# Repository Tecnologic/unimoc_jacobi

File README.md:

# Jacobi
36 V / 45 A (battery side, 100 A peak phase current) drive hardware of the [unimoc](https://github.com/Tecnologic/unimoc)
project, with optimised cooling. Jacobi is the motor controller (logic board and
power board); the firmware lives in the unimoc repository.

| | |
|---|---|
| Board directory (firmware) | `boards/unimoc/jacobi/` |
| Board name | `unimoc_jacobi` |
| Cyphal node name | `org.unimoc.jacobi` |
| EESM variant | Jacobi E |

Formerly `hardware_4850`.

### Naming

The unimoc nodes are named after inventors. Moritz Hermann Jacobi built the
first practical electric motor (1834, Königsberg) and drove a boat on the Neva
with it (1838): the first electric motor put to practical use as a drive, which
is what this board is for.

**Drives**

| Name | Class | Who |
|---|---|---|
| Barlow | small drive | Peter Barlow, whose "Barlow's wheel" (1822) was one of the first electric motors: tiny but turning |
| **Jacobi** | **36 V / 45 A drive (this board, H7)** | Moritz Hermann Jacobi, first practical electric motor (1834) and electric boat on the Neva (1838) |
| Dolivo | big drive | Michail Dolivo-Dobrowolsky invented the three-phase motor and the three-phase system (AEG, 1889), the basis of every FOC drive |

**Other nodes**

| Name | Role | Who |
|---|---|---|
| Zuse | VDC | Konrad Zuse built the first working programmable computer, so he's the brain |
| Drais | Pedal generator | Karl Drais invented the Laufmaschine (1817), the ancestor of the bicycle, powered by your own feet |
| Mercator | Steering | the map maker everyone navigates by |
| Gutenberg | Display | made information visible to everyone |
| Volta | BMS / battery | invented the battery (the voltaic pile, 1800) |
| Otto | Throttle | Nikolaus Otto, of the Otto engine: the classic gas pedal |

## Ratings and limits

What the hardware can do and where it stops. The numbers come from the
datasheets and rough loss and thermal estimates (calculations below), not from
measurements on a test bench. The reference load is the kids' quad: an MY1020
1600 W BLDC on 3 × 12 V lead-acid, which the controller already drives with
80 A peak phase current.

| | Rating | Limited by |
|---|---|---|
| Battery | **3 × 12 V lead-acid (36 V)**, up to 44 V while charging; Li-ion up to 10S (42 V) | 60 V FETs (NCEP6080AG), see below |
| Enable input (J501 pin 3 against pin 4) | **12–40 V**, switched battery voltage; 1–4 mA through a TLP291 optocoupler, 3750 Vrms isolation | input resistor R1115 (10k, 1206): 0.19 W at 44 V, 0.25 W rating |
| Battery current | **~45 A** (1600 W at 36 V) for minutes in still air; continuous only with better cooling | housing to air: 1600 W needs about 58 A peak phase current |
| Phase current, peak | **100 A** for seconds | motor saturation, FET losses |
| Phase current, continuous | **~50 A peak** in still air; with the housing bolted to a frame or in airflow, the 100 A motor limit comes first | housing to air (about 2.5 K/W) |
| Overcurrent trip | **120–130 A** | current sensing range ±160 A |
| Not suitable for | 48 V systems (13S/14S Li-ion, 4 × 12 V lead-acid) | 60 V FET rating |

### Target motors

| Motor | Saturation (peak phase current) | Fit |
|---|---|---|
| 60 mm stator motors | ~100 A | up to the rating |
| Hoverboard hub motors | ~55 A | about a third of the current range, fine resolution |
| MY1020 1600 W, 36 V (kids' quad) | not published, estimated 80–100 A | runs today at 80 A peak |

The MY1020 has no published saturation data. It can be measured with the
controller: lock the rotor, run a DC current on the d or q axis in steps
(0, 20, 40 … 120 A) and measure L = V / (di/dt) with a small voltage pulse.
Saturation starts where L falls by 20–30 %. Above that current the motor gives
little extra torque and mostly heat, so it is the useful current limit.

### Bridge voltage: why 36 V

The bridge uses **NCEP6080AG** (NCE, LCSC `C182469`, DFN5×6-8L), two in
parallel per switch, 12 per board. They are in stock and cost much less than
an 80 V part. From the LCSC product page (the datasheet PDF was not
reachable): 60 V, 80 A, R_DS(on) < 4.0 mΩ at 10 V (3.5 mΩ typ),
< 5.0 mΩ at 4.5 V, Qg 67 nC, Coss 680 pF, 85 W, Tj up to 150 °C.

| Battery | Max voltage | Margin to 60 V |
|---|---|---|
| 3 × 12 V lead-acid | ~44 V (charging) | 16 V: **fine** |
| 10S Li-ion | 42 V | 18 V: **fine** |
| 13S Li-ion | 54.6 V | 5 V: switching overshoot alone can use that, **no** |
| 14S Li-ion / 4 × 12 V | 58.8 V / ~58 V | **no** |

For 48 V the bridge needs 80 V FETs in the same footprint, e.g. the Infineon
**BSC040N08NS5** (80 V, 4.0 mΩ max, 121 A, marking `040N08NS`), which sits on
one of the existing prototype boards. Its R_DS(on) is the same as the NCE part;
its lower gate charge (43 nC) only shortens the switching edges a little. The
rest of the board already handles 48 V: the LM5008 supply runs from the battery
up to 95 V, and the voltage dividers reach 73.8 V full scale.

### Bridge losses

Two FETs in parallel per switch, sine current, 36 V, 20 kHz PWM, about 45 ns
switching edges (LM5109B at about 1 A into 2 × 67 nC, 1R1 gate resistors).
R_DS(on) is 4.0 mΩ max × 1.6 for Tj = 125 °C ≈ 6.4 mΩ. The factor 1.6 is
taken from the BSC040N08NS5 curve because the NCE datasheet was not
available; check it once the datasheet is in `datasheets/`.

| Phase current (peak) | Loss per FET | Loss per phase | Whole bridge |
|---|---|---|---|
| 50 A | ~1.3 W | ~5 W | ~16 W |
| 80 A | ~3 W | ~12 W | ~36 W |
| 100 A | ~4.5 W | ~18 W | ~54 W |

Conduction per FET is I_rms² × R_DS(on) / 8 (the phase current splits over two
FETs, and high and low side each conduct about half the time). Switching per
phase is ½ × V × I_avg × (t_on + t_off) × f_PWM with I_avg = 2/π × I_peak.

Using one FET per switch instead of two would save 6 FETs and about 180 mm²,
but it doubles the conduction loss at the same current (about 16 W per FET at
100 A peak). In the closed housing that comes straight off the continuous
current, so the board keeps two per switch.

### PCB manufacturing

The board is made by JLCPCB: 4 layers, **1 oz copper** on all layers (outer and
inner), standard process. The design rules in `jacobi.kicad_pro` follow the
[JLCPCB 4-layer capabilities](https://jlcpcb.com/capabilities/pcb-capabilities):

| Rule | Value |
|---|---|
| Min track width / clearance | 0.1 mm / 0.1 mm (the layout uses 0.2 mm / 0.2 mm or more) |
| Min via (diameter / drill) | 0.45 mm / 0.2 mm, annular ring 0.125 mm (the layout uses 0.6 / 0.3 mm and 0.8 / 0.4 mm) |
| Min copper to board edge | 0.3 mm (board setup: 0.5 mm) |
| Min hole to hole / hole clearance | 0.25 mm |
| Min silk text | 1.0 mm high, 0.15 mm line |

Net classes set the routing defaults (the high-current nets use pours, the track
width is only for stubs and pad entries):

| Class | Track / clearance / via | Nets |
|---|---|---|
| Power | 1.0 / 0.25 / 0.8 ⌀ 0.4 mm | +BATT, GNDPWR, phase and switch nodes |
| GateDrive | 0.5 / 0.2 / 0.6 ⌀ 0.3 mm | +12P, gate, HO/LO/HS/VSS, bootstrap |
| Dig Supply | 0.4 / 0.2 / 0.6 ⌀ 0.3 mm | +12V, +3V3, +1V2, +BATT_LOGIC, GNDD, buck nodes |
| Analog Supply | 0.4 / 0.2 / 0.6 ⌀ 0.3 mm | +3.3VA, +3.3VADC, GNDA, GND |
| Analog | 0.2 / 0.2 / 0.45 ⌀ 0.2 mm | current and voltage sense, temperature, ADC inputs |
| USB | 0.2 / 0.2 mm, pair gap 0.15 mm | USB_DP, USB_DM (impedance not yet checked) |
| Default | 0.15 / 0.15 / 0.45 ⌀ 0.2 mm | everything else |

### Cooling

The power board sits on an aluminium block the size of the board, which is
mounted to the floor of the G113T housing (115 × 90 mm). Today the bottom
copper is covered by solder mask, with thermal paste to the block and a
thermal pad to the housing.

| Step (per FET unless noted) | Rth | Note |
|---|---|---|
| Junction → case | ~1 K/W | datasheet class value |
| **Thermal vias** | **~3.3 K/W** | 38 × 0.4 mm, 25 µm plating: the largest step from FET to block |
| Solder mask + paste | ~1 K/W | 20 µm mask, 50 µm paste over about 100 mm² |
| Junction → block | **~5.5 K/W** | about 17 K at 80 A peak, about 25 K at 100 A peak |
| Block → housing (pad, whole board) | 0.05–0.1 K/W | 3–5 K at 54 W |
| **Housing → air (whole board)** | **~2–3 K/W** | 0.043 m² of housing in still air: **sets the continuous current** |

At 80 A peak the bridge loses about 36 W. In still air the housing would end up
far above any sensible temperature; it works because the peaks are short. The
block and housing hold about 600 J/K (10 mm block assumed), a time constant of
about 25 minutes, so 54 W (100 A peak) heats them by about 5 K per minute.

Continuous current for a block at ≤ 80 °C at 40 °C ambient (40 K):

| Housing to air | Allowed loss | Continuous phase current |
|---|---|---|
| Still air, ~2.5 K/W | ~16 W | ~50 A peak |
| Bolted to the frame or in airflow, ~0.5 K/W | ~80 W | ~120 A peak, so the 100 A motor limit comes first |

Improvements, biggest first:

1. **Housing to air.** Bolt the housing to the vehicle frame or a metal plate
   with paste, or add fins or airflow. This is worth more than all other steps
   together.
2. **Thermal vias.** Filled and capped vias (VIPPO) under the drain pad, as many
   as fit: about half the 3.3 K/W. The board stays 1 oz copper; the currents are
   carried by pours on all four layers, not by thicker copper.
3. **Block to housing.** Thin paste on flat surfaces instead of the thermal pad,
   screws near the FET rows.
4. **Copper spreading.** Large drain pours under each FET on the bottom and
   inner layers.

**Keep the isolation.** The bottom copper under the high-side FETs is at
+BATT, under the low-side FETs it is the phase node, and the block conducts.
The solder mask is the only insulation today. Opening the mask needs a defined
insulator instead (25 µm polyimide film or a 0.15–0.2 mm ceramic-filled pad);
thermally that is about the same as mask and paste, but the isolation is
reliable. Avoid metal-filled pastes there.

### Current sensing

One 0.5 mΩ 3920 shunt per phase (Yezhan DSLR-M-5-0.5F) in the phase output,
with an INA240A1 (gain 20):

| | |
|---|---|
| Range | 1.6 V / (20 × 0.5 mΩ) = **±160 A**, 10 mV/A |
| Overcurrent trip | 120–130 A, above the 100 A motor saturation |
| Offset | 25 µV max at the input = 0.05 A; calibrated at start, drift 0.25 µV/K |
| Resolution | about 0.08 A at 12 effective bits |
| Shunt loss | 1.6 W at 80 A peak, 2.5 W at 100 A peak (9 W part) |

Other combinations that were considered:

| Shunt + INA240 | Range | Why not |
|---|---|---|
| 0.4 mΩ + A1 | ±200 A | only needed for currents above 130 A, which the motors cannot use |
| 0.2 mΩ + A2 | ±160 A | same scaling, but 2.5× the offset in amps, and the A2 costs 1.60 € vs 0.25 € for a shunt |
| 0.2 mΩ + A1 | ±400 A | coarse at light load (about 0.2 A noise) |

## KiCad project

The logic board and the power board are combined in a single **KiCad 10** project:
[`jacobi.kicad_pro`](jacobi.kicad_pro).

| File | Content |
|---|---|
| [`jacobi.kicad_sch`](jacobi.kicad_sch) | Root sheet with the two board sheets |
| [`logic.kicad_sch`](logic.kicad_sch) | Logic board: sub-sheets [`power_supply`](power_supply.kicad_sch) and [`controller`](controller.kicad_sch); `controller` has the sub-sheets [`interfaces`](interfaces.kicad_sch) and [`analog`](analog.kicad_sch) |
| [`power.kicad_sch`](power.kicad_sch) | Power board: sub-sheet [`phase`](phase.kicad_sch), used three times for phase A/B/C |
| [`jacobi.kicad_pcb`](jacobi.kicad_pcb) | Both boards side by side: logic board on the left, power board on the right |
| [`footprints/jacobi.pretty`](footprints/jacobi.pretty) | Project footprint library: enclosure RND 455-00370, the Kelvin footprint of the phase shunt `R_Shunt_Yezhan_DSLR-5_3920_Kelvin`, and `LFPAK56_ThermalVias-1` and `C_2220_5650Metric`, which KiCad 10 no longer ships |

Since both boards are in one PCB file, the net names are kept apart by the
schematic hierarchy (`/logic/...`, `/power/...`). The board-to-board connectors
(J101/J102/J111 on the logic board, J103/J104/J110 on the power board) are **not** joined
electrically in the schematic, so each board keeps its own nets.

## PCB layout (rev 0.3)

Both boards are placed and routed for the released schematic (STM32H743
logic board, three-phase power board). DRC with schematic parity has no
errors and no open connections. Pictures: [logic board](docs/logic_board.png),
[its four layers](docs/logic_board_layers.png), [power board](docs/power_board.png),
[its four layers](docs/power_board_layers.png).

**Mechanics.** The logic board sits on top of the power board (104.05 mm apart
in x in the PCB file). The three M3 standoffs go through H104/H105/H107 (power)
and H102/H101/H103 (logic); H106 and the four housing pads of N101 screw the
power board to the cooling block. None of these moved. The three 2×5 pairs
J101/J103, J102/J104 and J111/J110 lie exactly on top of each other. J103 was
moved on the power board (room for the battery terminal), so J101 on the logic
board followed it to (187.37, 102.02). All parts of the logic board are on the
top side; only the three board-to-board headers are on the bottom.

**Power board, layers.**

| Layer | Use |
|---|---|
| Top | parts; per phase from top to bottom: GNDPWR source strip, switch node pour, +BATT drain strip; phase output pour from the shunt to the terminal; analog ground around the INA240s and dividers |
| Inner 1 | GNDPWR plane (analog `GND` plane right of x = 345 mm); the low-side gate pairs LO/VSS run in it |
| Inner 2 | +BATT plane with one switch node island per phase and the phase output pours; the high-side gate pairs HO/HS run in the switch node islands |
| Bottom | no parts: switch node islands under the low-side FETs, +BATT under the high-side FETs, phase output pours, GNDPWR elsewhere |

- Commutation loop per phase: C`x`04 (2220) in the centre column between the
  FET columns, +BATT pad on the drain strip, GNDPWR pad on a tongue of the
  source strip, the GNDPWR plane 0.2 mm below.
- Via fields (0.8 / 0.4 mm): about 15 per low-side FET source, 21 from each
  switch node to the shunt, 12 to 14 from the shunt to the phase terminal, 4 to 8
  per electrolytic capacitor pad. Pours of the power nets are 0.5 mm apart.
- Gate drive: 0.5 mm tracks with 45° corners, each gate resistor next to its
  gate pin, the gate/source pair of a FET on the same layer. The Kelvin net ties of the
  high-side sources (R`x`04, R`x`10) sit on the source pins; those of the
  low side (R`x`06, R`x`08) sit at the end of the source strip and at the
  commutation capacitor, because the gate track blocks the way to the pins.
- The second low-side FET of each phase has its gate parts in the centre
  column below the mounting holes H105/H106, which block the direct way.
- INA240: above its shunt, inputs facing it, the sense pair runs under the
  shunt and the amplifier. The phase outputs cross the analog signals only on
  inner layer 1, in the analog ground plane.
- Q401 moved by 0.34 mm onto the 26.4 mm cell pitch (it was off against Q403).
- The PWM inputs and the +12P trunk on the left are routed by hand (commit
  `59841ef`); the scripts take them from `scripts/layout/owner_tracks.json`.
  The +12P trunk is 1 mm wide where the clearance allows it, like +12V on the
  logic board.
- The bottom solder mask is open under the twelve FETs (bare, tinned drain
  copper towards the cooling block). An insulating pad has to sit in between.

**Logic board, layers.** Top: parts and most signals. Inner 1: GNDD plane,
GNDA island under the analog front end, the LDO and the analog connectors
(joined only through FB502). Inner 2: +3V3 plane, +3.3VADC island. Bottom:
signals, the board-to-board headers, MCU decoupling. Ground pours on top and
bottom, tied to the planes by stitching vias so that no piece is left as an
island. Under the input side of the optocoupler U1102 (J501 pins 3/4, R1115,
C1108, D1105) all four layers are free of pours (rule area `PWM_EN isolation`).

- The function groups sit together: 12 V buck (LM5008) top left behind J501,
  3.3 V buck right of the mounting hole, the +3.3VADC regulator below it next
  to J601, CAN between J1103 and J1104, the PWM series resistors next to J101.
- Both buck converters are routed with pours. Input capacitor, IC and diode
  form the hot loop: at the LM5008, C501 and D501 sit directly below the IC
  (VIN pad under pin 8, cathode under pin 1, both grounds next to each other,
  about 6 × 5 mm); at the LMR12010, C504 is left of the IC and D505 below it.
  Switch node, +12V and +3V3 are pours up to the inductors and output
  capacitors.
- +12V runs as a 1 mm trunk from the buck to J101 (the gate driver supply of
  the power board); the short branches to small pads are 0.5 mm.
- Each MCU supply pin pair has its 100 nF capacitor on the top side right at
  the pins.

- Edge connectors: left J501 (enable / battery), J1103 (CAN in), J1104 (CAN
  out), J602 (USB-C); right J601 (accelerator / brake, next to the +3.3VADC
  LDO), J701 (motor temperature), J1101 (Hall).
- Each analog input has its RC at the MCU pin: pins 32 to 36 above the MCU,
  pins 15 to 25 right of it. The 20 MHz oscillator sits below that, on GNDD.
- The status LEDs (RUN, ERROR, FW, PWM) sit at the bottom edge next to the
  board marking, 6 mm apart, each with its name below it.
- The PWM series resistors R606–R611 sit on the top side next to J101.

**How it is made.** The layout is generated: `scripts/layout/build.py` places
the parts, draws the pours, via fields and the gate drive, and routes the
small signals with the grid router in `scripts/layout/router.py` (0.1 mm
grid, 45° tracks). `power.py` and `logic.py` hold the positions. To change the
layout, change the script and run it again (KiCad 10 Python with numpy, scipy
and Pillow; the paths at the top of `build.py` point to a working copy), or
edit the PCB in KiCad and accept that the script no longer reproduces it.

**Silkscreen.** Designators only (1.0 mm); values and order numbers are on
the fabrication layer. A designator stands right next to its part only where
it cannot be read as belonging to a neighbour (in line with the part, nothing
closer). Dense groups get a framed block of their designators beside them, in
the same arrangement as the parts: the RC rows right of the MCU, the RC
columns above it, the 12 V regulator, the Hall filters and two of the voltage
dividers. On the power board every FET is labelled the same way: its two gate
resistors in line with their rows, the FET name upright on the outer side of
its column. Net ties carry no designator. Each connector carries its
designator and function (`J501 ENABLE`, `J1103 CAN IN`, ...). Both boards are
marked `UNIMOC JACOBI` / `rev 0.3` in two lines; the status LEDs sit next to
the marking with their names (RUN, ERROR, FW, PWM). Pictures:
[logic](docs/logic_silkscreen.png), [power](docs/power_silkscreen.png).

The bottom side of the logic board names every pin of the external connectors
at the pin itself (BATT+, VIN LOGIC, PWM EN±, CAN GND/L/H, DCC/ACC, NTC,
HALL A–C, +5V, SWD), so the harness can be soldered and checked from below
([picture](docs/logic_board_bottom.png)). The board-to-board headers are not
labelled there. The schematic order number `Part#` is copied into each
footprint (hidden) for the BOM.

**Before ordering, check on the bench or in KiCad:**

- The bottom of the power board carries bare drain copper under the FETs
  (+BATT and the switch nodes), gate signals in vias (tented) and the THT pins
  of the terminals J105–J109 stick out. The cooling block needs the insulating
  pad and clearance for those pins.
- The height under the logic board (pin header and socket give about 11 mm)
  against the electrolytic capacitors (10.5 mm) and the terminal screws.
- The 3D fit in the housing and the direction of the edge connectors.

## Schematic notes

The schematic was ahead of the PCB while the logic board was redrawn for the
H743; the notes on what changed stay here.

- **MCU: STM32H743VIT6** (LQFP100, 2 MB flash, LCSC `C114409`) instead of the
  STM32F730R8. It sits on the `controller` sheet (now A3) and connects by net
  labels; the old wires end in labels of the same names. Added decoupling
  C613–C622; C603 is now 2.2 µF (VCAP). Pin plan and open points:
  [docs/h743_logic_board.md](docs/h743_logic_board.md).
- **Simple analog front end.** The op-amp filters of the logic board are gone
  (the three `current_filters` sheets with low pass and AC high pass per phase,
  and the U701 filters for Vdc and the bridge NTC). What is left on the `analog`
  sheet:
  - Ia/Ib/Ic: 220R / 2n2 RC from the INA240 outputs (R717–R719, C713–C715)
  - Va/Vb/Vc: 220R / 2n2 RC (R720–R722, C716–C718), the same as the currents
  - Vdc: 4k7 / 10n RC (R705/C704)
  - +12P (gate driver supply): 4k7 / 10n RC (R723/C719)
  - bridge NTC: pull-up R703 with C701, then a 4k7 / 10n RC (R704/C703)
  - motor temperature unchanged

  The filter values are a first guess.
- **Voltage sensing on the power board.** The dividers for the phase voltages
  and Vdc (47k / 2k2 0.1 %, with 1 nF; R101–R108, C101–C104) sit on the power
  board and go to the logic board over a third 2×5 connector, J110 → J111
  (VSENSE). The old Vdc divider R701/R702/C702 on the logic board is gone.
- **Gate driver supply sense.** A 10k / 2k2 divider (R109/R110, C105) on +12P
  at the drivers goes over pin 3 of the PWM connector (J103 → J101) to PC5. No
  12 V is routed to the analog part.
- **Power board present.** J110 pin 9 is GND on the power board; on the logic
  board it is pulled up (R612, 10k) to PE4 (`PWR_DET`, low = present).
- **Bridge NTC to GND on the power board.** TH101 has its low side on the power
  board GND; only the high side goes through J104 pin 8. J104 pin 10 is now GND.
- **One shunt per phase.** 0.5 mΩ 3920 (Yezhan DSLR-M-5-0.5F, LCSC
  `C41382689`) with Kelvin sense pads instead of three 2 mΩ 2512 in
  parallel, read by an INA240A1 (gain 20): ±160 A.
- **USB-C** instead of mini-B: HRO TYPE-C-31-M-12 (LCSC `C165948`, 16 pins,
  USB 2.0), 5k1 on CC1/CC2 (R613/R614) as a device. SBU not connected.
- **PWM_EN through an optocoupler.** The PWM_EN jumper J1102 is gone. The
  enable input is a TLP291 (U1102) on the `interfaces` sheet that pulls PE15
  high. J501 (`Enable`, now 4-pin JST PH) carries, from pin 1: `+BATT_LOGIC`
  (battery +), the LM5008 supply (VIN), `PWM_EN_IN` (opto LED +, **12–40 V**)
  and `PWM_EN_RTN` (opto LED return, battery −). The LED path is 10k (R1115)
  with 10n (C1108) across the LED and a 1N4148W (D1105) against reverse
  polarity. The output has a 510R collector resistor, a 10k pulldown (R1116)
  and 10n (C1109). `PWM_EN_RTN` is not connected to `GNDD`, so the enable
  line is isolated and its current stays in its own wire pair, which keeps
  noise out on a cart with four drives. Keep the LED side clear of copper from
  the output side under U1102 (5 mm creepage). On the bench bridge pins 1–2,
  put battery + on pin 3 and battery − on pin 4. On the cart switch pin 2
  (logic) and pin 3 (phases).
- **`+48V` is now `+BATT_LOGIC`.** The board is no longer 48 V compatible
  (60 V FETs), so the logic board supply net (J101 pin 1, J501 pin 1) is named
  after the battery. It stays a separate net from `+BATT` on the power board.
- **No aux bridge.** The EESM excitation and brake chopper are out of scope for
  this board; a separate module will do that.

## Production data

[`production/jlcpcb/`](production/jlcpcb) has one folder per board with the
Gerber and drill files as a zip for the JLCPCB upload and the placement file
(`*_cpl.csv`). Order as 4 layers, 1.6 mm, 1 oz outer and inner copper, vias
tented. `python3 scripts/layout/export.py` splits `jacobi.kicad_pcb` into the
two boards and writes these files again.

The old KiCad 5 data (F730 logic board, as manufactured) is in
[`production/legacy_kicad5/`](production/legacy_kicad5).

## Other folders

| Folder | Content |
|---|---|
| [`datasheets/`](datasheets) | Component datasheets |
| [`docs/`](docs) | Pictures of the [logic board](docs/logic_board.png) and the [power board](docs/power_board.png) (layout rev 0.3), [H743 logic board concept](docs/h743_logic_board.md) |
| [`scripts/layout/`](scripts/layout) | The scripts that generate the PCB layout and the production data |
| [`mechanical/`](mechanical) | DXF exports of the power board, the cooler drawing, [`enclosure/`](mechanical/enclosure) with STEP and DXF views of the RND 455-00370 |

## Conversion notes (KiCad 5.1 → KiCad 10)

- All symbols are updated from the KiCad 10 library; no KiCad 5 symbol
  graphics are left. The unused `SolderJumper_2_Open` was dropped. The old
  bitmaps of the other board on the `logic` and `power` sheets are removed.
- The KiCad 5 schematic had other values than the PCB on the power board (the
  PCB was changed later). The schematic now follows the PCB: Q`x`01–Q`x`04
  `NCEP6080AG`, C`x`07/C`x`09 `56u`, R`x`03–R`x`10 `1R1`. Their old `Part#`
  order numbers were removed and still have to be filled in.
- Parts that KiCad 10 dropped or renamed:
  - Footprints `LFPAK56_ThermalVias-1` and `C_2220_5650Metric` are now in the
    project library, copied from the PCB.
  - The 3D model of the 2220 capacitor now points to `C_2220_5750Metric`.
  - Symbols are relinked: `Device:CP` → `Device:C_Polarized`,
    `Device:Ferrite_Bead_Small` → `Device:FerriteBead_Small`,
    `Device:Jumper_NO_Small` → `Jumper:Jumper_2_Small_Open`.

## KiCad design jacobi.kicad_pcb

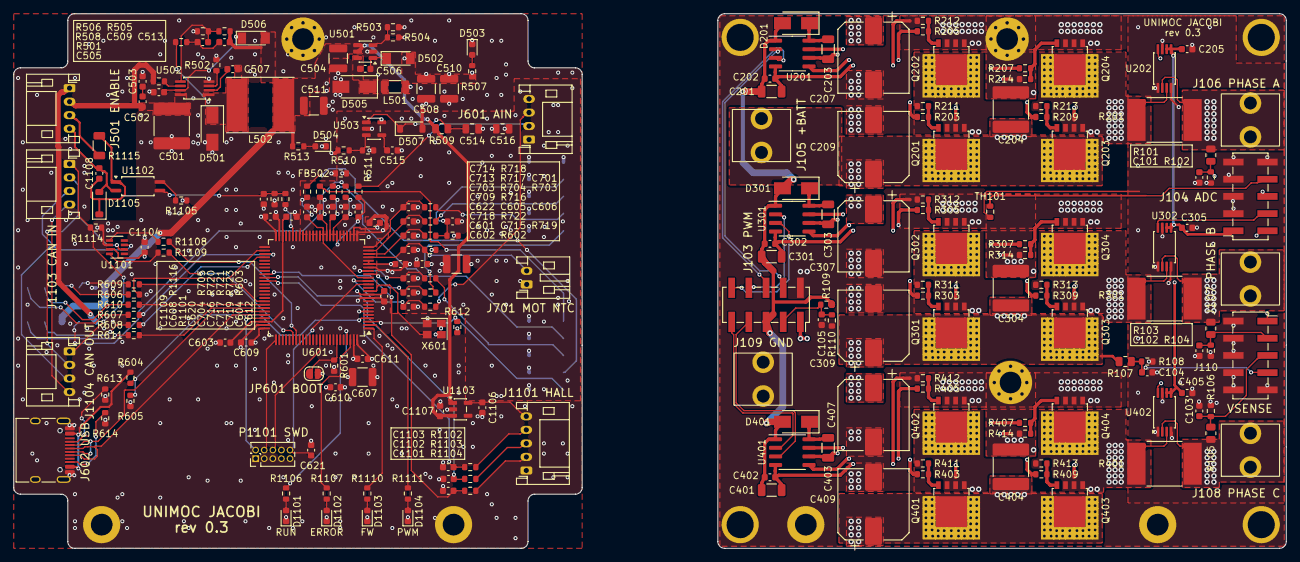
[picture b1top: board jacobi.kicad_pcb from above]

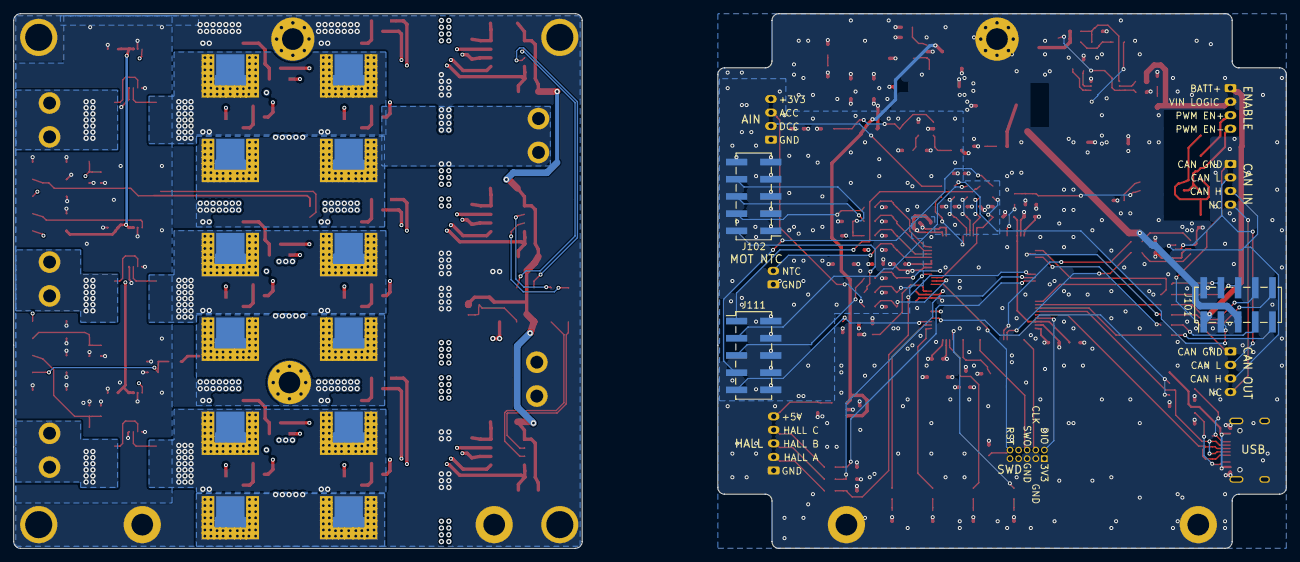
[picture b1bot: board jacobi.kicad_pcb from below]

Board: 4 copper layers, 188.1 x 79.0 mm, 248 parts (3 on the bottom side), 157 nets.

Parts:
C101, C102, C103, C104: 1n; C_0603_1608Metric
C105, C202, C205, C302, C305, C402, C405, C502, C503, C506, C507, C601, C602, C604, C605, C608, C609, C610, C611, C612, C621, C622, C701, C709, C1101, C1102, C1103, C1104: 100n; C_0603_1608Metric
C201, C203, C301, C303, C401, C403: 10u; C_1206_3216Metric
C204, C304, C404, C501: 10u; C_2220_5650Metric
C207, C209, C307, C309, C407, C409: 56u; CP_Elec_10x10
C504, C508, C510, C511: 22u; C_1210_3225Metric
C505, C1106, C1107: 1u; C_0603_1608Metric
C509, C513: 4n7; C_0603_1608Metric
C514, C516: 10u; C_0805_2012Metric
C515, C703, C704, C719, C1108, C1109: 10n; C_0603_1608Metric
C603, C620: 2u2; C_0603_1608Metric
C606, C607: 10u; C_1210_3225Metric
C713, C714, C715, C716, C717, C718: 2n2; C_0603_1608Metric
D201, D301, D401, D501, D505: SS110R3G; D_SMA
D502, D506: PMLL4153; D_MiniMELF
D503: 3V3; LED_0603_1608Metric
D504: 12V; LED_0603_1608Metric
D507: BZT52C15; D_SOD-123
D1101: RUN; LED_0603_1608Metric
D1102: ERROR; LED_0603_1608Metric
D1103: FW; LED_0603_1608Metric
D1104: PWM; LED_0603_1608Metric
D1105: 1N4148W; D_SOD-123
FB502: Ferrite_Bead_Small; R_0603_1608Metric
H101, H105, H106: GND; MountingHole_3.2mm_M3_Pad_Via
H102, H103, H104, H107: GND; MountingHole_3.2mm_M3_ISO14580_Pad
J101: PWM; PinHeader_2x05_P2.54mm_Vertical_SMD
J102: ADC; PinHeader_2x05_P2.54mm_Vertical_SMD
J103: PWM; PinSocket_2x05_P2.54mm_Vertical_SMD
J104: ADC; PinSocket_2x05_P2.54mm_Vertical_SMD
J105: +; Terminal_M3_XFCN_TT34086077-0910
J106: A; Terminal_M3_XFCN_TT34086077-0910
J107: B; Terminal_M3_XFCN_TT34086077-0910
J108: C; Terminal_M3_XFCN_TT34086077-0910
J109: GND; Terminal_M3_XFCN_TT34086077-0910
J110: VSENSE; PinSocket_2x05_P2.54mm_Vertical_SMD
J111: VSENSE; PinHeader_2x05_P2.54mm_Vertical_SMD
J501: Enable; JST_PH_S4B-PH-K_1x04_P2.00mm_Horizontal
J601: AIN; JST_PH_S4B-PH-K_1x04_P2.00mm_Horizontal
J602: TYPE-C-31-M-12; USB_C_Receptacle_HRO_TYPE-C-31-M-12
J701: MOT_TEMP; JST_PH_S2B-PH-K_1x02_P2.00mm_Horizontal
J1101: HALL; JST_PH_S5B-PH-K_1x05_P2.00mm_Horizontal
J1103: CAN_IN; JST_PH_S4B-PH-K_1x04_P2.00mm_Horizontal
J1104: CAN_Out; JST_PH_S4B-PH-K_1x04_P2.00mm_Horizontal
JP601: BTLDR; SolderJumper-2_P1.3mm_Open_RoundedPad1.0x1.5mm
L501: 4u7; L_1206_3216Metric
L502: 330u; L_Taiyo-Yuden_NR-80xx_HandSoldering
N101: Housing_Pad; RND-455-00370
P1101: SWD; PinHeader_2x05_P1.27mm_Vertical
Q201, Q202, Q203, Q204, Q301, Q302, Q303, Q304, Q401, Q402, Q403, Q404: NCEP6080AG; LFPAK56_ThermalVias-1
R101, R103, R105, R107: 47k 0.1%; R_0805_2012Metric
R102, R104, R106, R108: 2k2 0.1%; R_0603_1608Metric
R109, R510, R612, R1116: 10k; R_0603_1608Metric
R110: 2k2; R_0603_1608Metric
R201, R301, R401: 0m5; R_Shunt_Yezhan_DSLR-5_3920_Kelvin
R203, R205, R207, R209, R303, R305, R307, R309, R403, R405, R407, R409, R606, R607, R608, R609, R610, R611: 1R1; R_0603_1608Metric
R204, R206, R208, R210, R304, R306, R308, R310, R404, R406, R408, R410: NetTie_2; NetTie-2_SMD_Pad0.5mm
R211, R212, R213, R214, R311, R312, R313, R314, R411, R412, R413, R414: 47k; R_0603_1608Metric
R501: 220k; R_0603_1608Metric
R502, R508: 100k; R_0603_1608Metric
R503, R505, R601, R602, R603, R605: 11k; R_0603_1608Metric
R504: 34k; R_0603_1608Metric
R506: 2k7; R_0603_1608Metric
R507, R1101, R1102, R1103, R1104, R1105, R1106, R1107, R1110, R1111: 510R; R_0603_1608Metric
R509: 47R; R_0805_2012Metric
R511: 22k; R_0603_1608Metric
R513: 3k3; R_0603_1608Metric
R604, R704, R705, R723: 4k7; R_0603_1608Metric
R613, R614: 5k1; R_0603_1608Metric
R703, R716: 10k 0.1%; R_0603_1608Metric
R717, R718, R719, R720, R721, R722: 220R; R_0603_1608Metric
R1108, R1109, R1114: 11R; R_0603_1608Metric
R1115: 10k; R_1206_3216Metric
TH101: NTC 10k; R_0603_1608Metric
U201, U301, U401: LM5109BMA; SOIC-8_3.9x4.9mm_P1.27mm
U202, U302, U402: INA240A1PWR; TSSOP-8_4.4x3mm_P0.65mm
U501: LMR12010Y; SOT-23-6
U502: LM5008; MSOP-8_3x3mm_P0.65mm
U503: LP2985-33DBVR; SOT-23-5
U601: STM32H743VIT6; LQFP-100_14x14mm_P0.5mm
U1101: TCAN334; SOT-23-8
U1102: TLP291; SOIC-4_4.55x2.6mm_P1.27mm
U1103: AP2204K-5.0; SOT-23-5
X601: Q33310F70051500; Oscillator_SMD_Abracon_ASE-4Pin_3.2x2.5mm

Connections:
+1V2: C603.1, C620.1, U601.48 (VCAP), U601.73 (VCAP)
+3.3VA: C205.1, C305.1, C405.1, J104.1, U202.5, U202.6, U302.5, U302.6, U402.5, U402.6
+3.3VADC: C516.1, C605.1, C606.1, C622.1, J102.1, J601.4, R703.2, R716.2, U503.5, U601.20 (VREF+), U601.21 (VDDA)
+3V3: C508.1, C510.1, C601.1, C607.1, C608.1, C609.1, C610.1, C611.1, C612.1, C1104.1, D502.2 (A), JP601.2 (B), L501.2, P1101.1, R504.2, R507.2, R510.1, R612.1, R1105.2, U601.6 (VBAT), U601.11 (VDD), U601.27 (VDD), U601.50 (VDD), U601.75 (VDD), U601.100 (VDD), U1101.3 (VCC), X601.1 (EN), X601.4 (Vdd)
+12P: C201.1, C202.1, C301.1, C302.1, C401.1, C402.1, D201.2 (A), D301.2 (A), D401.2 (A), J103.5, R109.1, U201.1 (VDD), U301.1 (VDD), U401.1 (VDD)
+12V: C504.1, C511.1, C513.1, C1107.1, D506.2 (A), J101.5, L502.2, R505.2, R509.1, R513.1, U501.4, U501.5, U1103.1, U1103.3
+BATT: C204.1, C207.1, C209.1, C304.1, C307.1, C309.1, C404.1, C407.1, C409.1, J103.1, J105.1 (Pin_1_1), Q201.5 (D), Q203.5 (D), Q301.5 (D), Q303.5 (D), Q401.5 (D), Q403.5 (D), R107.1
+BATT_LOGIC: J101.1, J501.1
/logic/PWM_EN_IN: J501.3, R1115.1
/logic/PWM_EN_RTN: C1108.2, D1105.2 (A), J501.4, U1102.2
/logic/controller/Ia: J102.6, R717.2
/logic/controller/Ib: J102.4, R718.2
/logic/controller/Ic: J102.2, R719.2
/logic/controller/PWR_DET: J111.9, R612.2, U601.3 (PE4)
/logic/controller/PwmAH: J101.4, R609.1
/logic/controller/PwmAL: J101.6, R606.1
/logic/controller/PwmBH: J101.8, R610.1
/logic/controller/PwmBL: J101.10, R607.1
/logic/controller/PwmCH: J101.9, R611.1
/logic/controller/PwmCL: J101.7, R608.1
/logic/controller/Temp+: C701.1, J102.8, R703.1, R704.2
/logic/controller/V12P: J101.3, R723.2
/logic/controller/Va: J111.1, R720.2
/logic/controller/Vb: J111.3, R721.2
/logic/controller/Vc: J111.5, R722.2
/logic/controller/VdcIn: J111.7, R705.2
/logic/controller/analog/AIN_ACC: C602.1, R602.2, U601.15 (PC0)
/logic/controller/analog/AIN_DCC: C604.1, R603.2, U601.32 (PC4)
/logic/controller/analog/BrdgTemp: C703.2, R704.1, U601.23 (PA1)
/logic/controller/analog/IaDC: C713.2, R717.1, U601.24 (PA2)
/logic/controller/analog/IbDC: C714.2, R718.1, U601.25 (PA3)
/logic/controller/analog/IcDC: C715.2, R719.1, U601.17 (PC2_C)
/logic/controller/analog/MotTemp: C709.1, J701.2, R716.1, U601.22 (PA0)
/logic/controller/analog/V12PDC: C719.2, R723.1, U601.33 (PC5)
/logic/controller/analog/VaDC: C716.2, R720.1, U601.35 (PB1)
/logic/controller/analog/VbDC: C717.2, R721.1, U601.34 (PB0)
/logic/controller/analog/VcDC: C718.2, R722.1, U601.18 (PC3_C)
/logic/controller/interfaces/CAN_RXD: R1109.2, U601.81 (PD0)
/logic/controller/interfaces/CAN_TXD: R1108.2, U601.82 (PD1)
/logic/controller/interfaces/HallA: C1101.1, R1104.1, U601.59 (PD12)
/logic/controller/interfaces/HallB: C1102.1, R1103.1, U601.60 (PD13)
/logic/controller/interfaces/HallC: C1103.1, R1102.1, U601.61 (PD14)
/logic/controller/interfaces/LED_ERROR: R1107.2, U601.98 (PE1)
/logic/controller/interfaces/LED_MODE: R1110.2, U601.1 (PE2)
/logic/controller/interfaces/LED_PWM: R1111.2, U601.2 (PE3)
/logic/controller/interfaces/LED_RUN: R1106.2, U601.97 (PE0)
/logic/controller/interfaces/PWM_EN: R1101.2, U601.45 (PE15)
/logic/controller/interfaces/SWCLK: P1101.4, U601.76 (PA14)
/logic/controller/interfaces/SWDIO: P1101.2, U601.72 (PA13)
/logic/controller/interfaces/SWO: P1101.6, U601.89 (PB3)
/logic/controller/mcu/AIN_VDC: C704.2, R705.1, U601.16 (PC1), U601.36 (PB2)
/logic/controller/mcu/USB_DM: J602.A7 (D-), J602.B7 (D-), U601.70 (PA11)
/logic/controller/mcu/USB_DP: J602.A6 (D+), J602.B6 (D+), U601.71 (PA12)
/logic/controller/mcu/USB_VBUS: R604.2, R605.2, U601.4 (PE5)
/logic/controller/mcu/\RESET: C621.1, P1101.10, U601.14 (NRST)
/logic/controller/usb/VBUS: J602.A4 (VBUS), J602.A9 (VBUS), J602.B4 (VBUS), J602.B9 (VBUS), R604.1
/power/I_A: J104.6, U202.8
/power/I_B: J104.4, U302.8
/power/I_C: J104.2, U402.8
/power/PHASE_A: J106.1 (Pin_1_1), R101.1, R201.1, R201.2, U202.2
/power/PHASE_B: J107.1 (Pin_1_1), R103.1, R301.1, R301.2, U302.2
/power/PHASE_C: J108.1 (Pin_1_1), R105.1, R401.1, R401.2, U402.2
/power/PWM_AH: J103.4, U201.2 (HI)
/power/PWM_AL: J103.6, U201.3 (LI)
/power/PWM_BH: J103.8, U301.2 (HI)
/power/PWM_BL: J103.10, U301.3 (LI)
/power/PWM_CH: J103.9, U401.2 (HI)
/power/PWM_CL: J103.7, U401.3 (LI)
/power/V12P_SNS: C105.2, J103.3, R109.2, R110.1
/power/VSENSE_A: C101.2, J110.1, R101.2, R102.1
/power/VSENSE_B: C102.2, J110.3, R103.2, R104.1
/power/VSENSE_C: C103.2, J110.5, R105.2, R106.1
/power/VSENSE_DC: C104.2, J110.7, R107.2, R108.1
/power/phase_a/HO: R203.2, R209.2, U201.7 (HO)
/power/phase_a/HS: C203.2, R204.1, R210.1, U201.6 (HS)
/power/phase_a/LO: R205.2, R207.2, U201.5 (LO)
/power/phase_a/VSS: C201.2, C202.2, R206.1, R208.1, U201.4 (VSS)
/power/phase_b/HO: R303.2, R309.2, U301.7 (HO)
/power/phase_b/HS: C303.2, R304.1, R310.1, U301.6 (HS)
/power/phase_b/LO: R305.2, R307.2, U301.5 (LO)
/power/phase_b/VSS: C301.2, C302.2, R306.1, R308.1, U301.4 (VSS)
/power/phase_c/HO: R403.2, R409.2, U401.7 (HO)
/power/phase_c/HS: C403.2, R404.1, R410.1, U401.6 (HS)
/power/phase_c/LO: R405.2, R407.2, U401.5 (LO)
/power/phase_c/VSS: C401.2, C402.2, R406.1, R408.1, U401.4 (VSS)
GND: C101.1, C102.1, C103.1, C104.1, C205.2, C305.2, C405.2, J104.3, J104.5, J104.7, J104.9, J104.10, J110.2, J110.4, J110.6, J110.8, J110.9, J110.10, R102.2, R104.2, R106.2, R108.2, TH101.2, U202.1, U202.4, U202.7, U302.1, U302.4, U302.7, U402.1, U402.4, U402.7
GNDA: C514.2, C515.2, C516.2, C602.2, C604.2, C605.2, C606.2, C622.2, C701.2, C703.1, C704.1, C709.2, C713.1, C714.1, C715.1, C716.1, C717.1, C718.1, C719.1, FB502.1, J102.3, J102.5, J102.7, J102.9, J102.10, J111.2, J111.4, J111.6, J111.8, J111.10, J601.1, J701.1, R511.2, U503.2, U601.19 (VSSA)
GNDD: C501.2, C503.2, C504.2, C505.1, C508.2, C510.2, C511.2, C601.2, C603.2, C607.2, C608.2, C609.2, C610.2, C611.2, C612.2, C620.2, C621.2, C1101.2, C1102.2, C1103.2, C1104.2, C1106.2, C1107.2, C1109.2, D501.2 (A), D503.1 (K), D504.1 (K), D505.2 (A), D507.2 (A), D1101.1 (K), D1102.1 (K), D1103.1 (K), D1104.1 (K), FB502.2, H101.1 (1_1), H102.1 (1_1), H103.1 (1_1), J101.2, J602.A1 (GND), J602.A12 (GND), J602.B1 (GND), J602.B12 (GND), J602.SH (SHIELD), J1101.1, P1101.3, P1101.5, R502.1, R503.1, R506.1, R601.1, R605.1, R613.1, R614.1, R1114.2, R1116.2, U501.2, U502.4, U601.10 (VSS), U601.26 (VSS), U601.49 (VSS), U601.74 (VSS), U601.99 (VSS), U1101.2 (GND), U1103.2, X601.2 (GND)
GNDPWR: C105.1, C204.2, C207.2, C209.2, C304.2, C307.2, C309.2, C404.2, C407.2, C409.2, H104.1 (1_1), H105.1 (1_1), H106.1 (1_1), H107.1 (1_1), J103.2, J109.1 (Pin_1_1), N101.1 (PAD_1), Q202.1 (S), Q202.2 (S), Q202.3 (S), Q204.1 (S), Q204.2 (S), Q204.3 (S), Q302.1 (S), Q302.2 (S), Q302.3 (S), Q304.1 (S), Q304.2 (S), Q304.3 (S), Q402.1 (S), Q402.2 (S), Q402.3 (S), Q404.1 (S), Q404.2 (S), Q404.3 (S), R110.2, R206.2, R208.2, R212.2, R214.2, R306.2, R308.2, R312.2, R314.2, R406.2, R408.2, R412.2, R414.2
unnamed: C502.2, C503.1
unnamed: C509.1, C513.2, R508.2
unnamed: C1109.1, R1101.1, R1116.1, U1102.3
unnamed: C203.1, D201.1 (K), U201.8 (HB)
unnamed: C303.1, D301.1 (K), U301.8 (HB)
unnamed: C403.1, D401.1 (K), U401.8 (HB)
unnamed: C507.1, D501.1 (K), L502.1, R508.1, U502.1
unnamed: C506.2, D502.1 (K), U501.1
unnamed: D503.2 (A), R507.1
unnamed: D504.2 (A), R513.2
unnamed: C506.1, D505.1 (K), L501.1, U501.6
unnamed: C505.2, D506.1 (K), U502.7
unnamed: C514.1, D507.1 (K), R509.2, U503.1
unnamed: D1101.2 (A), R1106.1
unnamed: D1102.2 (A), R1107.1
unnamed: D1103.2 (A), R1110.1
unnamed: D1104.2 (A), R1111.1
unnamed: C1108.1, D1105.1 (K), R1115.2, U1102.1
unnamed: J104.8, TH101.1
unnamed: C501.1, C502.1, J501.2, R501.2, U502.8
unnamed: J601.2, R603.1
unnamed: J601.3, R602.1
unnamed: J602.A5 (CC1), R613.2
unnamed: J602.B5 (CC2), R614.2
unnamed: J1101.2, R1104.2
unnamed: J1101.3, R1103.2
unnamed: J1101.4, R1102.2
unnamed: C1106.1, J1101.5, U1103.5
unnamed: J1103.1, J1104.1, R1114.1
unnamed: J1103.2, J1104.2, U1101.6 (CANL)
unnamed: J1103.3, J1104.3, U1101.7 (CANH)
unnamed: J1103.4, J1104.4
unnamed: JP601.1 (A), R601.2, U601.94 (BOOT0)
unnamed: Q201.4 (G), R203.1, R211.1
unnamed: Q201.1 (S), Q201.2 (S), Q201.3 (S), Q202.5 (D), Q203.1 (S), Q203.2 (S), Q203.3 (S), Q204.5 (D), R201.4, R204.2, R210.2, R211.2, R213.2
unnamed: Q202.4 (G), R205.1, R212.1
unnamed: Q203.4 (G), R209.1, R213.1
unnamed: Q204.4 (G), R207.1, R214.1
unnamed: Q301.4 (G), R303.1, R311.1
unnamed: Q301.1 (S), Q301.2 (S), Q301.3 (S), Q302.5 (D), Q303.1 (S), Q303.2 (S), Q303.3 (S), Q304.5 (D), R301.4, R304.2, R310.2, R311.2, R313.2
unnamed: Q302.4 (G), R305.1, R312.1
unnamed: Q303.4 (G), R309.1, R313.1
unnamed: Q304.4 (G), R307.1, R314.1
unnamed: Q401.4 (G), R403.1, R411.1
unnamed: Q401.1 (S), Q401.2 (S), Q401.3 (S), Q402.5 (D), Q403.1 (S), Q403.2 (S), Q403.3 (S), Q404.5 (D), R401.4, R404.2, R410.2, R411.2, R413.2
unnamed: Q402.4 (G), R405.1, R412.1
unnamed: Q403.4 (G), R409.1, R413.1
unnamed: Q404.4 (G), R407.1, R414.1
unnamed: R1105.1, U1102.4
unnamed: R201.3, U202.3
unnamed: R301.3, U302.3
unnamed: R401.3, U402.3
unnamed: R503.2, R504.1, U501.3
unnamed: C507.2, U502.2
unnamed: C509.2, R505.1, R506.2, U502.5
unnamed: R502.2, U502.3
unnamed: R501.1, U502.6
unnamed: C515.1, U503.4
unnamed: R510.2, R511.1, U503.3
unnamed: R609.2, U601.67 (PA8)
unnamed: R610.2, U601.68 (PA9)
unnamed: R611.2, U601.69 (PA10)
unnamed: R606.2, U601.52 (PB13)
unnamed: R607.2, U601.53 (PB14)
unnamed: R608.2, U601.54 (PB15)
unnamed: U601.12 (PH0), X601.3 (OUT)
unnamed: R1109.1, U1101.4 (RXD)
unnamed: R1108.1, U1101.1 (TXD)
